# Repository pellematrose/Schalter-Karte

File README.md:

# Schalter-Karte

Eine Schalter-Karte als Ersatz für Sicherungsautomaten in 24V-Systemen.

---

## 🔧 Gedachte Verwendung
Das Modul ist gedacht als **Schaltbare Sicherung für den Pluspfad** und ist damit Vergleichbar mit einem klassischen **Sicherungsautomaten**.

An die Schraubklemme **J1** wird **24V** angeschlossen. Die zweite Schraubposition kann zum durchverdrahten mit weiteren Modulen genutzt werden.  

Eine **Autosicherung** schützt die angeschlossene Last, die an **J2** angeschlossen wird.

Über den **Schiebeschalter** kann zwischen **Strompfad A und B** umgeschaltet werden:

- **Schalterstellung A**  
  → Verbraucher **A EIN**, **B AUS**

- **Schalterstellung B**  
  → Verbraucher **B EIN**, **A AUS**

Die Anschlüsse **A** und **B** an **J2** werden jeweils über den Schalter auf **24V** geschaltet.

Der angeschlossene Verbraucher erhält **GND extern**.

---

## 📏 Technische Daten

- Versorgungsspannung: 24V (+-20%)
- Laststrom: 4A (Schiebeschalter, Leiterbahnen)
- **PCB Maße:** 17,5 mm × 77 mm  
- Die Abmessungen orientieren sich an einem **Sicherungsautomaten**

---

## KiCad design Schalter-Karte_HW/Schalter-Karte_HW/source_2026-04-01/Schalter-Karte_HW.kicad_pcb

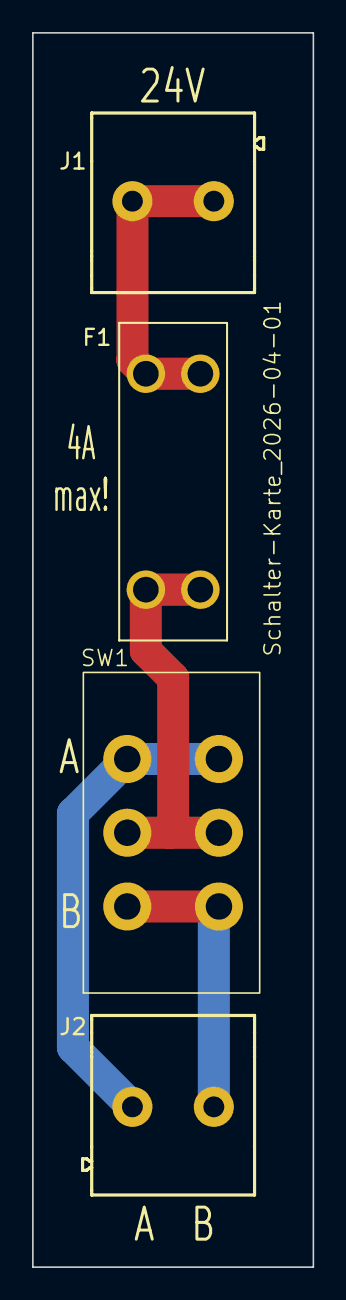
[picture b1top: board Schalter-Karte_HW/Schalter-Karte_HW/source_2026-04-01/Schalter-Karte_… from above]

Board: 2 copper layers, 17.5 x 77.0 mm, 6 parts (1 on the bottom side), 4 nets.

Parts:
F1: 3557-2; Fuse Holder Littelfuse ATOF 287
J1, J2: MKDS_3-2_5.08; MKDS_3_2_508
PCB1: _PCB
Repo1: _Repository
SW1: L102011MS02Q; L10101_Schiebeschalter

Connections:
+24V: F1.1, J1.1, J1.2
+24V_sicher: F1.2, SW1.2 (B), SW1.5 (B)
unnamed: J2.1, SW1.1 (A), SW1.6 (C)
unnamed: J2.2, SW1.3 (C), SW1.4 (A)

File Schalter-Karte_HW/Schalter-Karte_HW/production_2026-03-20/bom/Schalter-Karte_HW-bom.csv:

"Reference","Value","Footprint","LCSC","Digikey","Mouser"
"F1","3557-2","_PS_LIB_CON:Fuse Holder Littelfuse ATOF 287","","",""
"J1","MKDS_3-2_5.08","_PS_LIB_CON:MKDS_3_2_508","","277-1027-ND",""
"J2","MKDS_3-3_5.08","_PS_LIB_CON:MKDS_3_3_508","","277-1028-ND",""
"SW1","L101011MS02Q","_PS_LIB_MECH:L10101_Schiebeschalter","","CKC5106-ND",""

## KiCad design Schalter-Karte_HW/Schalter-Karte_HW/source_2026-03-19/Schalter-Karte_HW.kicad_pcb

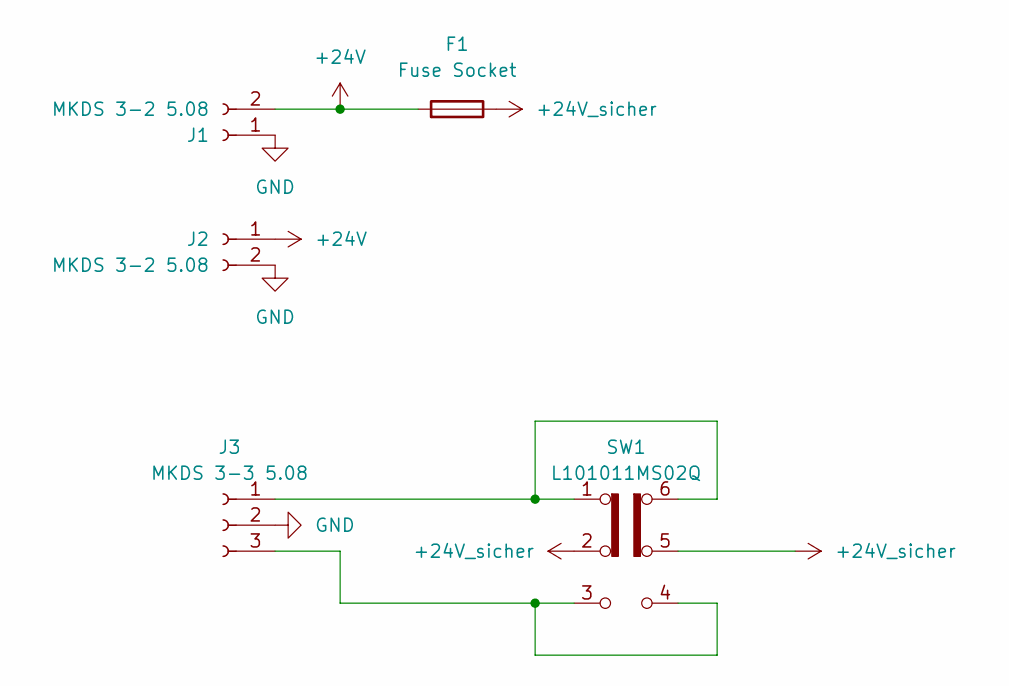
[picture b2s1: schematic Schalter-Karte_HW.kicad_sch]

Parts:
F1: Fuse Socket; Fuse Holder Littelfuse ATOF 287
J1, J2: MKDS 3-2 5.08; MKDS_3_2_508
J3: MKDS 3-3 5.08; MKDS_3_3_508
SW1: L101011MS02Q; L10101_Schiebeschalter

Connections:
+24V: F1.2, J1.2, J2.1
+24V_sicher: F1.1, SW1.2 (B), SW1.5 (B)
GND: J1.1, J2.2, J3.2
unnamed: J3.1, SW1.1 (A), SW1.6 (C)
unnamed: J3.3, SW1.3 (C), SW1.4 (A)

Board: 2 copper layers, 5 parts (0 on the bottom side), 5 nets, no tracks yet.

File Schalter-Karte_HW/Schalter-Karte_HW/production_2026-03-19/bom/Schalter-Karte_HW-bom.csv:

"Reference","Value","Footprint","LCSC"
"F1","Fuse Socket","_PS_LIB_CON:Fuse Holder Littelfuse ATOF 287",""
"J1","MKDS 3-2 5.08","_PS_LIB_CON:MKDS_3_2_508",""
"J2","MKDS 3-2 5.08","_PS_LIB_CON:MKDS_3_2_508",""
"J3","MKDS 3-3 5.08","_PS_LIB_CON:MKDS_3_3_508",""
"SW1","L101011MS02Q","_PS_LIB_MECH:L10101_Schiebeschalter",""

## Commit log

2026-03-20 3d render added
2026-03-20 assembly drawings added
2026-03-22 gnd entfernt
2026-03-23 added geber zip file
2026-03-23 schalter typ angepasst
2026-04-05 final version
2026-04-21 update 3d render

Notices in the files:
Schalter-Karte_HW/Schalter-Karte_HW/source_2026-03-20/Schalter-Karte_HW.kicad_sch:
Licensed under CERN-OHL-S v2
© 2026 Per-Simon Saal
Schalter-Karte_HW/Schalter-Karte_HW/source_2026-04-01/Schalter-Karte_HW.kicad_sch:
CERN-OHL-S v2
